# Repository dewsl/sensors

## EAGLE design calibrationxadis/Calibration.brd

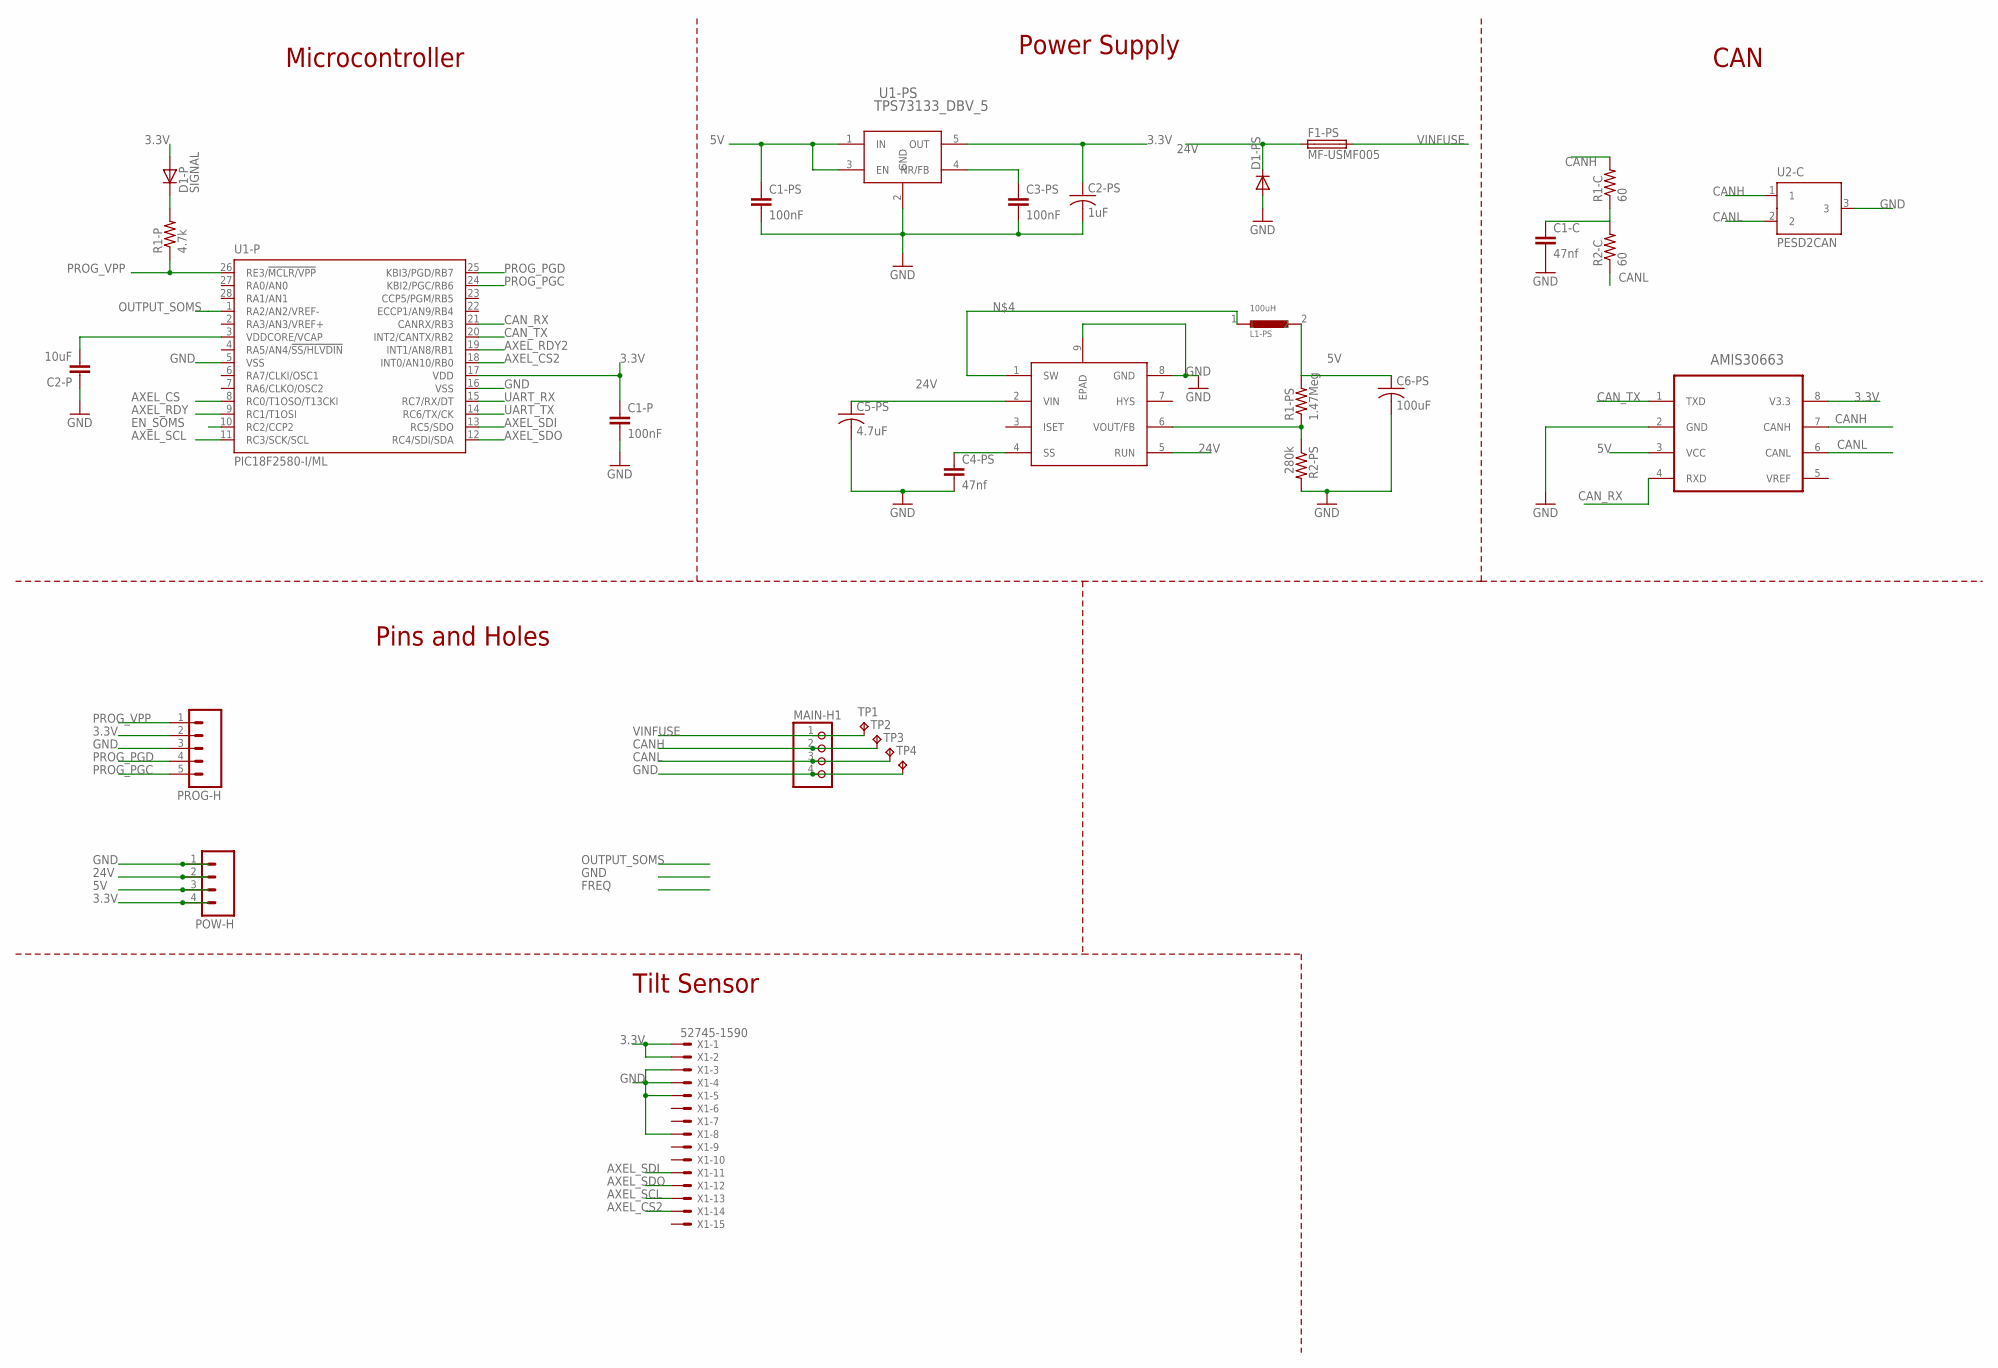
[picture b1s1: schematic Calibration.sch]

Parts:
C1-C, C4-PS: 47nf; C0805
C1-P, C1-PS, C3-PS: 100nF; C0603
C2-P: 10uF; C0603
C2-PS: 1uF; C0402
C5-PS: 4.7uF; C1206K
C6-PS: 100uF; C1210K
D1-P: SIGNAL; DIODE-0603
D1-PS: DIODE-DO-214AC; DO-214AC
F1-PS: MF-USMF005; 1210
L1-PS: 100uH; 1210
MAIN-H1: PINHD-1X04_2.54; 1X04
POW-H: M041X04_NO_SILK; 1X04_NO_SILK
PROG-H: M05PTH; 1X05
R1-C, R2-C: 60; R0805
R1-P: 4.7k; R0603
R1-PS: 1.47Meg; R0805
R2-PS: 280k; R0805
TP1, TP2, TP3, TP4: TPTP10SQ; TP10SQ
U1-P: PIC18F2580-I/ML; QFN28-ML_6X6MM
U1-PS: TPS73133_DBV_5; DBV5
U2: AMIS30663CAN; SOIC8
U2-C: PESD2CAN; SOT23
U2-PS: LTC3631-5; MSOP8E
X1: 52745-1590

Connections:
3.3V: C1-P.1, C2-PS.1, D1-P.A, POW-H.4, PROG-H.2, U1-P.17 (VDD), U1-PS.5 (OUT), U2.8 (V3.3), X1.1, X1.2
5V: C1-PS.1, C6-PS.1, L1-PS.2, POW-H.3, R1-PS.2, U1-PS.1 (IN), U1-PS.3 (EN), U2.3 (VCC)
24V: C5-PS.1, D1-PS.1 (C), F1-PS.1, POW-H.2, U2-PS.2 (VIN), U2-PS.5 (RUN)
AXEL_CS: U1-P.8 (RC0/T1OSO/T13CKI)
AXEL_CS2: U1-P.18 (INT0/AN10/RB0), X1.14
AXEL_RDY: U1-P.9 (RC1/T1OSI)
AXEL_RDY2: U1-P.19 (INT1/AN8/RB1)
AXEL_SCL: U1-P.11 (RC3/SCK/SCL), X1.13
AXEL_SDI: U1-P.13 (RC5/SDO), X1.11
AXEL_SDO: U1-P.12 (RC4/SDI/SDA), X1.12
CANH: MAIN-H1.2, R1-C.2, TP2.TP, U2.7 (CANH), U2-C.1
CANL: MAIN-H1.3, R2-C.1, TP3.TP, U2.6 (CANL), U2-C.2
CAN_RX: U1-P.21 (CANRX/RB3), U2.4 (RXD)
CAN_TX: U1-P.20 (INT2/CANTX/RB2), U2.1 (TXD)
EN_SOMS: U1-P.10 (RC2/CCP2)
GND: C1-C.2, C1-P.2, C1-PS.2, C2-P.1, C2-PS.2, C3-PS.2, C4-PS.2, C5-PS.2, C6-PS.2, D1-PS.2 (A), MAIN-H1.4, POW-H.1, PROG-H.3, R2-PS.2, TP4.TP, U1-P.5 (VSS), U1-P.16 (VSS), U1-PS.2 (GND), U2.2 (GND), U2-C.3, U2-PS.8 (GND), U2-PS.9 (EPAD), X1.3, X1.4, X1.5, X1.8
unnamed: C1-C.1, R1-C.1, R2-C.2
unnamed: L1-PS.1, U2-PS.1 (SW)
unnamed: C3-PS.1, U1-PS.4 (NR/FB)
unnamed: R1-PS.1, R2-PS.1, U2-PS.6 (VOUT/FB)
unnamed: D1-P.C, R1-P.2
unnamed: C4-PS.1, U2-PS.4 (SS)
unnamed: C2-P.2, U1-P.3 (VDDCORE/VCAP)
OUTPUT_SOMS: U1-P.1 (RA2/AN2/VREF-)
PROG_PGC: PROG-H.5, U1-P.24 (KBI2/PGC/RB6)
PROG_PGD: PROG-H.4, U1-P.25 (KBI3/PGD/RB7)
PROG_VPP: PROG-H.1, R1-P.1, U1-P.26 (RE3/!MCLR/VPP)
UART_RX: U1-P.15 (RC7/RX/DT)
UART_TX: U1-P.14 (RC6/TX/CK)
VINFUSE: F1-PS.2, MAIN-H1.1, TP1.TP

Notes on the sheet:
Microcontroller
Power Supply
CAN
Pins and Holes
Tilt Sensor

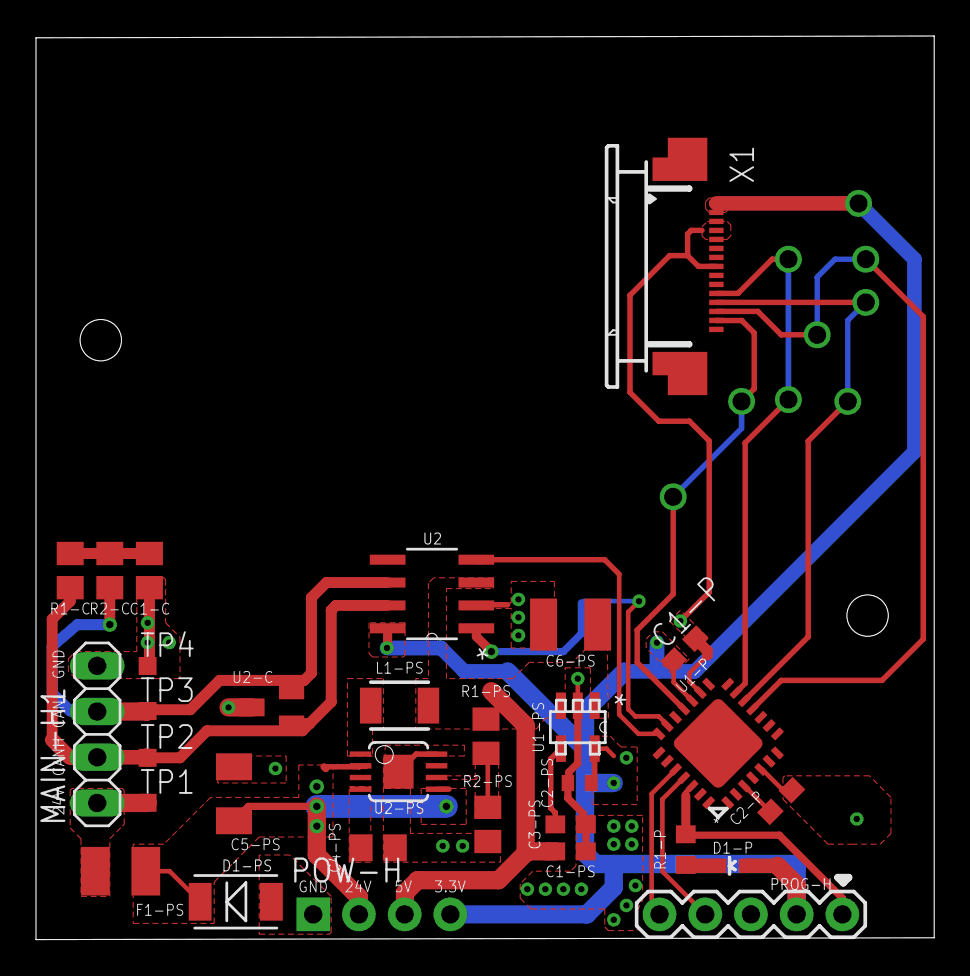
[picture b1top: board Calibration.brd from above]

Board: 2 copper layers, 49.9 x 50.2 mm, 31 parts (0 on the bottom side), 23 nets.

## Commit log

2018-03-06 added basic teensy can codes.
2018-05-18 Added the pic codes for the v3 sensors that support both v2 and v3 calibration methods.
2020-02-19 update get_axel1raw and update function names
2020-02-27 update initialize
2020-03-04 update axel_initialize
2020-03-04 Updated message id
2020-03-04 update adis code for v5 sensors
2020-08-10 +added surficialtilt arduino code
2021-12-15 add calibration and update sensor codes for version 4&5 sensors
2022-03-29 setting up MPLAB and XC8
2022-03-29 added adis schematic board
2025-06-17 updated calibration script
    same file, just cleaned and updated some function. also added print column for failing parameters xyz
2025-06-18 Update updated_Ensalada_CALIB.py
    same file, just cleaned and updated some function. also added print column for failing parameters xyz

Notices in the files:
parts and their libraries:
SparkFun-Connectors: Licensing: CC v3.0 Share-Alike You are welcome to use this library for commercial purposes.
